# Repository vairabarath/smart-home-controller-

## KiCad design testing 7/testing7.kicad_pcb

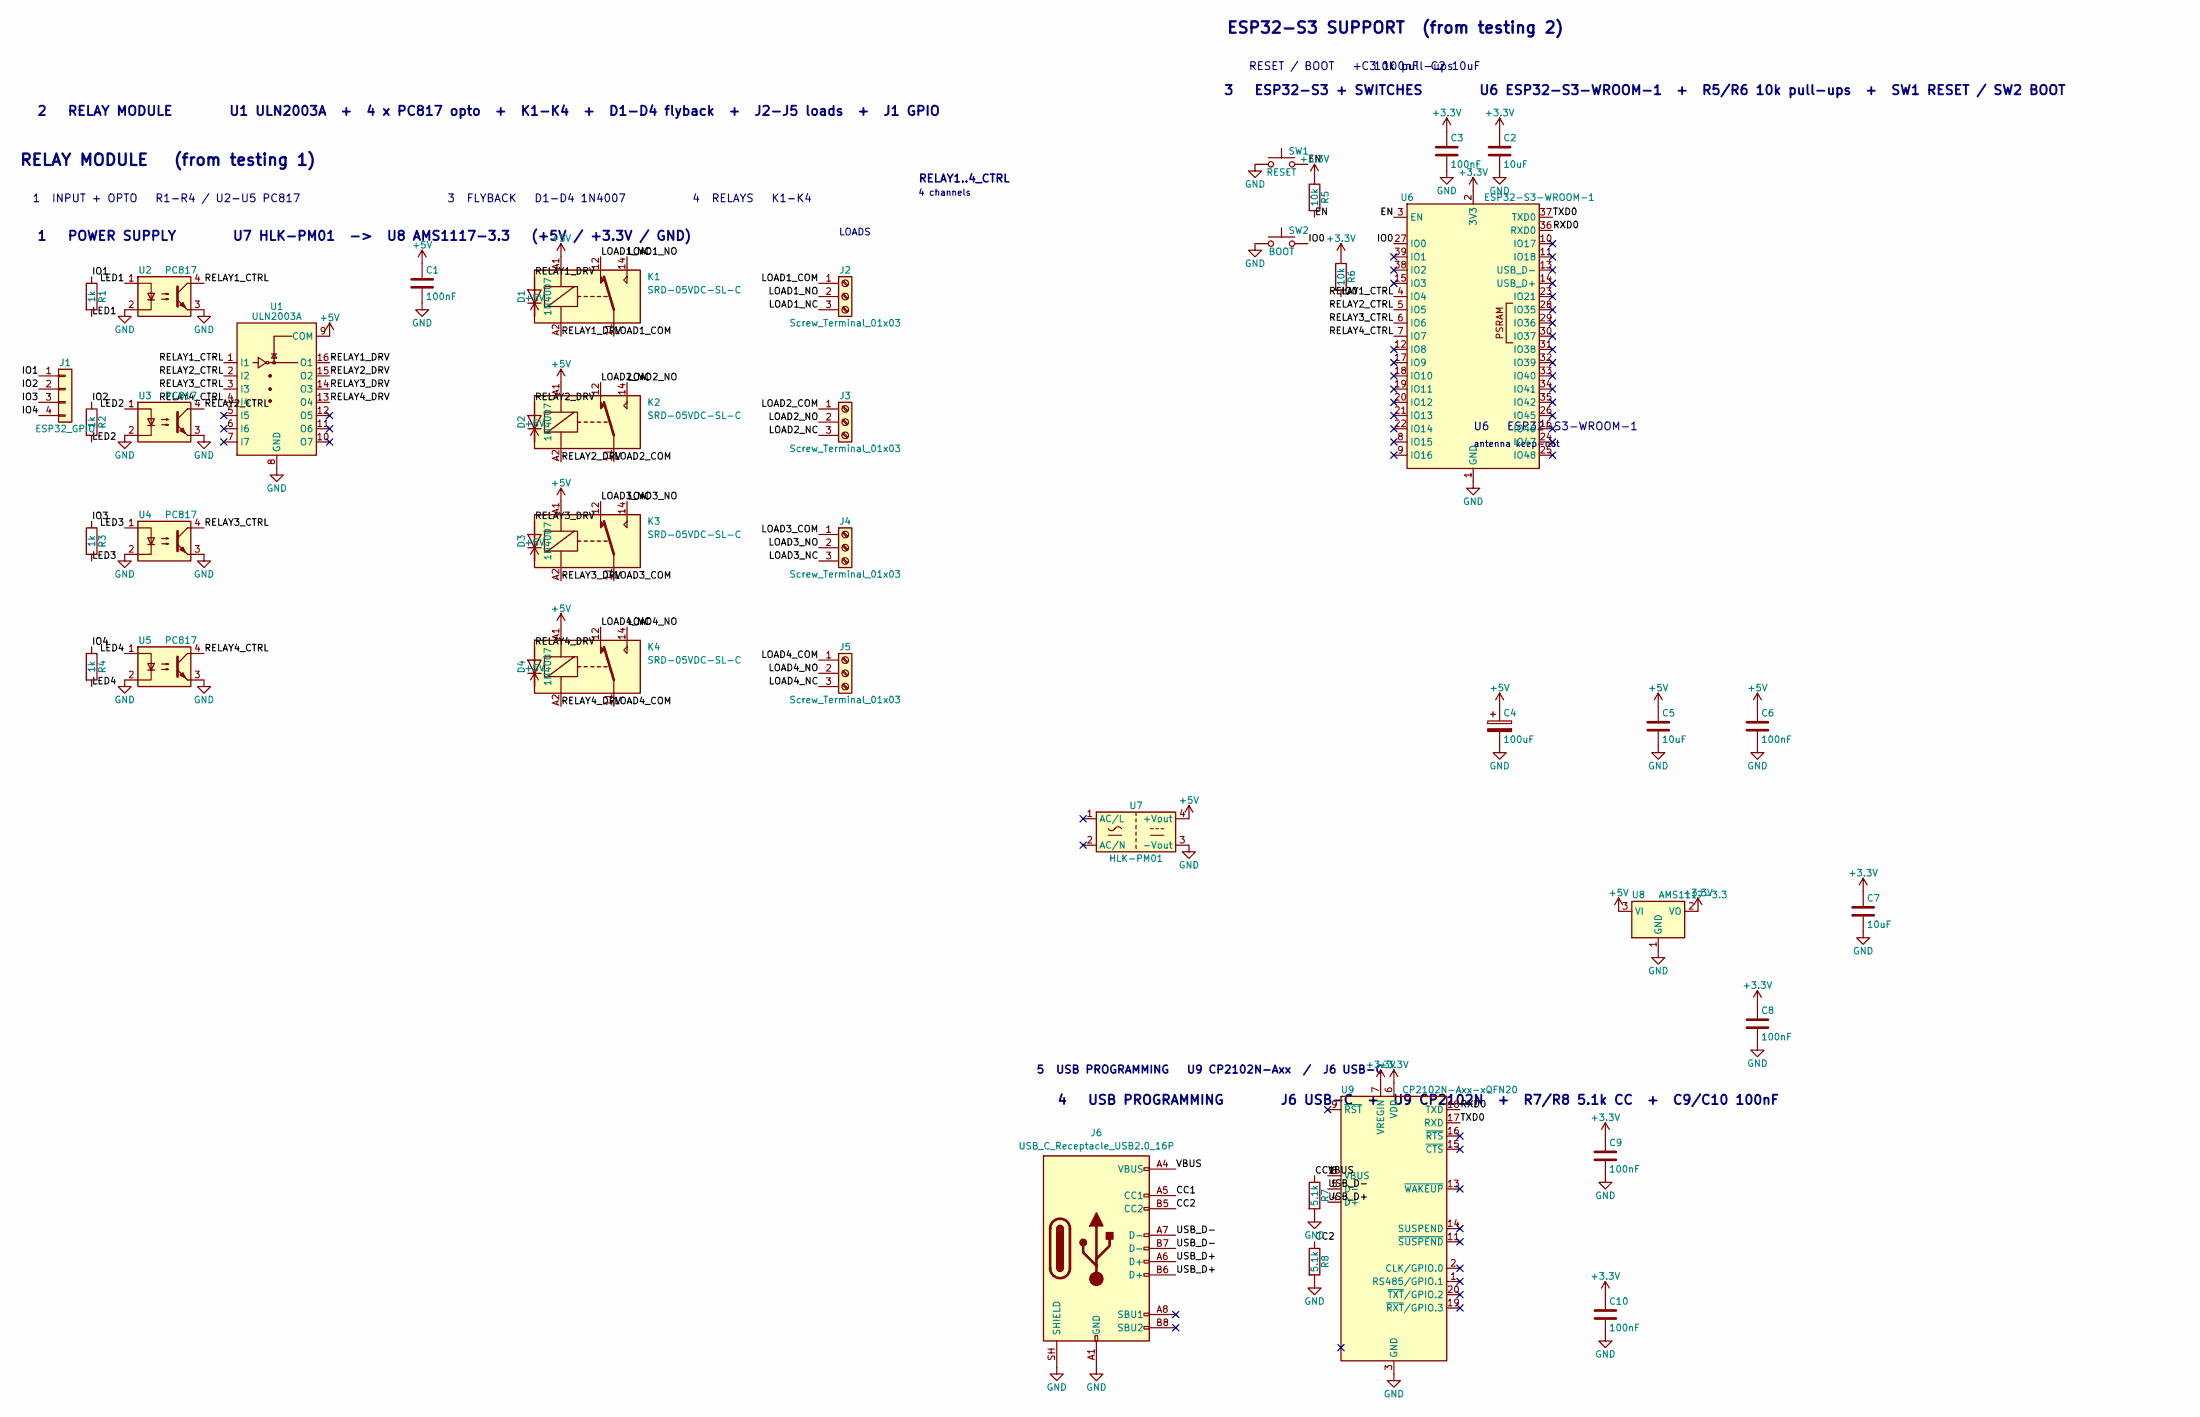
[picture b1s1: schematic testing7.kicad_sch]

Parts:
C1, C3, C6, C8, C9, C10: 100nF; C_0402_1005Metric
C2, C5, C7: 10uF; C_0805_2012Metric
C4: 100uF; CP_Radial_D10.0mm_P5.00mm
D1, D2, D3, D4: 1N4007; D_DO-41_SOD81_P10.16mm_Horizontal
J1: ESP32_GPIO; PinHeader_1x04_P2.54mm_Vertical
J2, J3, J4, J5: Screw_Terminal_01x03; TerminalBlock_Phoenix_MKDS-1,5-3_1x03_P5.00mm_Horizontal
J6: USB_C_Receptacle_USB2.0_16P; USB_C_Receptacle_GCT_USB4105-xx-A_16P_TopMnt_Horizontal
K1, K2, K3, K4: SRD-05VDC-SL-C; Relay_SPDT_Omron_G2RL-1-E
R1, R2, R3, R4: 1k; R_Axial_DIN0207_L6.3mm_D2.5mm_P7.62mm_Horizontal
R5, R6: 10k; R_0402_1005Metric
R7, R8: 5.1k; R_0402_1005Metric
SW1: RESET; SW_SPST_TL3342
SW2: BOOT; SW_SPST_TL3342
U1: ULN2003A; DIP-16_W7.62mm
U2, U3, U4, U5: PC817; DIP-4_W7.62mm
U6: ESP32-S3-WROOM-1
U7: HLK-PM01; Converter_ACDC_Hi-Link_HLK-PMxx
U8: AMS1117-3.3; SOT-223-3_TabPin2
U9: CP2102N-Axx-xQFN20; QFN-20-1EP_5x5mm_P0.65mm_EP3.35x3.35mm

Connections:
+3.3V: C2.1, C3.1, C7.1, C8.1, C9.1, C10.1, R5.1, R6.1, U6.2 (3V3), U8.2 (VO), U9.6 (VDD), U9.7 (VREGIN)
+5V: C1.1, C4.1, C5.1, C6.1, D1.1 (K), D2.1 (K), D3.1 (K), D4.1 (K), K1.A1, K2.A1, K3.A1, K4.A1, U1.9 (COM), U7.4 (+Vout), U8.3 (VI)
/CC1: J6.A5 (CC1), R7.1
/CC2: J6.B5 (CC2), R8.1
/EN: R5.2, SW1.2, U6.3 (EN)
/IO0: R6.2, SW2.2, U6.27 (IO0)
/IO1: J1.1, R1.1
/IO2: J1.2, R2.1
/IO3: J1.3, R3.1
/IO4: J1.4, R4.1
/LED1: R1.2, U2.1
/LED2: R2.2, U3.1
/LED3: R3.2, U4.1
/LED4: R4.2, U5.1
/LOAD1_COM: J2.1, K1.11
/LOAD1_NC: J2.3, K1.12
/LOAD1_NO: J2.2, K1.14
/LOAD2_COM: J3.1, K2.11
/LOAD2_NC: J3.3, K2.12
/LOAD2_NO: J3.2, K2.14
/LOAD3_COM: J4.1, K3.11
/LOAD3_NC: J4.3, K3.12
/LOAD3_NO: J4.2, K3.14
/LOAD4_COM: J5.1, K4.11
/LOAD4_NC: J5.3, K4.12
/LOAD4_NO: J5.2, K4.14
/RELAY1_CTRL: U1.1 (I1), U2.4, U6.4 (IO4)
/RELAY1_DRV: D1.2 (A), K1.A2, U1.16 (O1)
/RELAY2_CTRL: U1.2 (I2), U3.4, U6.5 (IO5)
/RELAY2_DRV: D2.2 (A), K2.A2, U1.15 (O2)
/RELAY3_CTRL: U1.3 (I3), U4.4, U6.6 (IO6)
/RELAY3_DRV: D3.2 (A), K3.A2, U1.14 (O3)
/RELAY4_CTRL: U1.4 (I4), U5.4, U6.7 (IO7)
/RELAY4_DRV: D4.2 (A), K4.A2, U1.13 (O4)
/RXD0: U6.36 (RXD0), U9.18 (TXD)
/TXD0: U6.37 (TXD0), U9.17 (RXD)
/USB_D+: J6.A6 (D+), J6.B6 (D+), U9.4 (D+)
/USB_D-: J6.A7 (D-), J6.B7 (D-), U9.5 (D-)
/VBUS: J6.A4 (VBUS), J6.A9 (VBUS), J6.B4 (VBUS), J6.B9 (VBUS), U9.8 (VBUS)
GND: C1.2, C2.2, C3.2, C4.2, C5.2, C6.2, C7.2, C8.2, C9.2, C10.2, J6.A1 (GND), J6.A12 (GND), J6.B1 (GND), J6.B12 (GND), J6.SH (SHIELD), R7.2, R8.2, SW1.1, SW2.1, U1.8 (GND), U2.2, U2.3, U3.2, U3.3, U4.2, U4.3, U5.2, U5.3, U6.1 (GND), U6.40 (GND), U6.41 (GND), U7.3 (-Vout), U8.1 (GND), U9.3 (GND), U9.12 (GND), U9.21 (GND)

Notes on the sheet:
RESET / BOOT + 10k pull-ups
antenna keep-out
C3 100nF C2 10uF
ESP32-S3 SUPPORT (from testing 2)
LOADS
RELAY1..4_CTRL
4 RELAYS K1-K4
4 channels
RELAY MODULE (from testing 1)
3 FLYBACK D1-D4 1N4007
1 INPUT + OPTO R1-R4 / U2-U5 PC817
U6 ESP32-S3-WROOM-1
5 USB PROGRAMMING U9 CP2102N-Axx / J6 USB-C
1 POWER SUPPLY U7 HLK-PM01 -> U8 AMS1117-3.3 (+5V / +3.3V / GND)
2 RELAY MODULE U1 ULN2003A + 4 x PC817 opto + K1-K4 + D1-D4 flyback + J2-J5 loads + J1 GPIO
3 ESP32-S3 + SWITCHES U6 ESP32-S3-WROOM-1 + R5/R6 10k pull-ups + SW1 RESET / SW2 BOOT
4 USB PROGRAMMING J6 USB-C + U9 CP2102N + R7/R8 5.1k CC + C9/C10 100nF

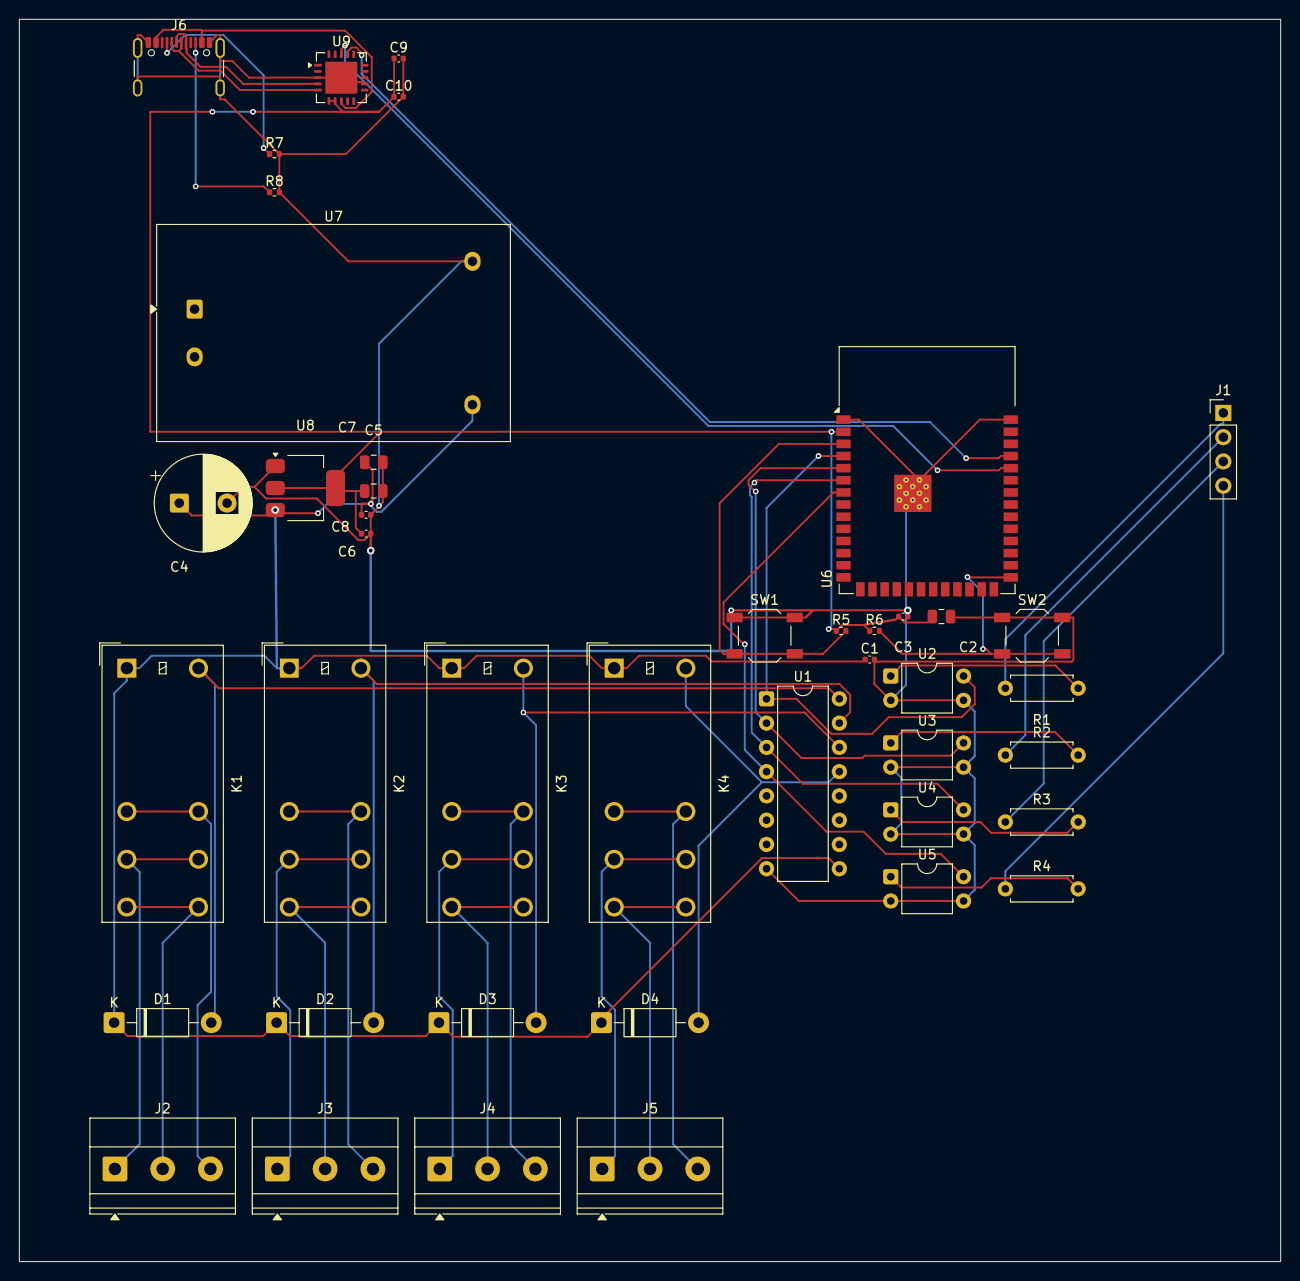
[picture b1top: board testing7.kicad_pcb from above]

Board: 2 copper layers, 132.0 x 130.0 mm, 43 parts (0 on the bottom side), 40 nets.

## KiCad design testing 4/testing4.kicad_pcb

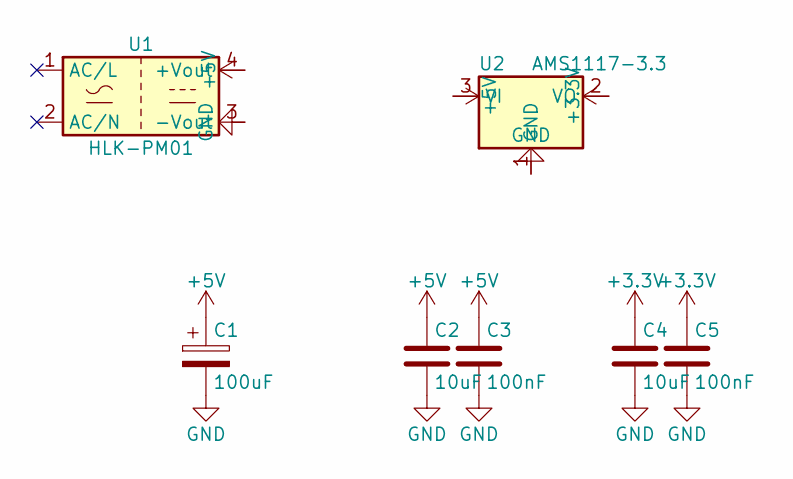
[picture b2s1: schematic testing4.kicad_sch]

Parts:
C1: 100uF; CP_Radial_D10.0mm_P5.00mm
C2, C4: 10uF; C_0805_2012Metric
C3, C5: 100nF; C_0402_1005Metric
U1: HLK-PM01; Converter_ACDC_Hi-Link_HLK-PMxx
U2: AMS1117-3.3; SOT-223-3_TabPin2

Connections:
+3.3V: C4.1, C5.1, U2.2 (VO)
+5V: C1.1, C2.1, C3.1, U1.4 (+Vout), U2.3 (VI)
GND: C1.2, C2.2, C3.2, C4.2, C5.2, U1.3 (-Vout), U2.1 (GND)

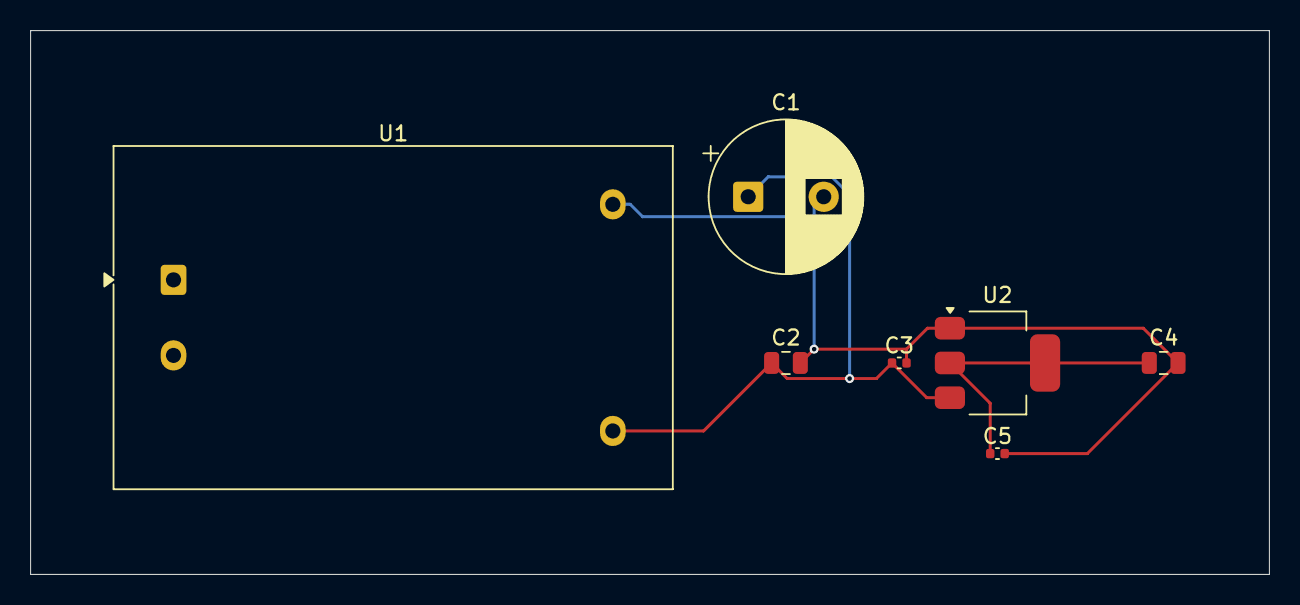
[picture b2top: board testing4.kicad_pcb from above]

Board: 2 copper layers, 82.0 x 36.0 mm, 7 parts (0 on the bottom side), 3 nets.

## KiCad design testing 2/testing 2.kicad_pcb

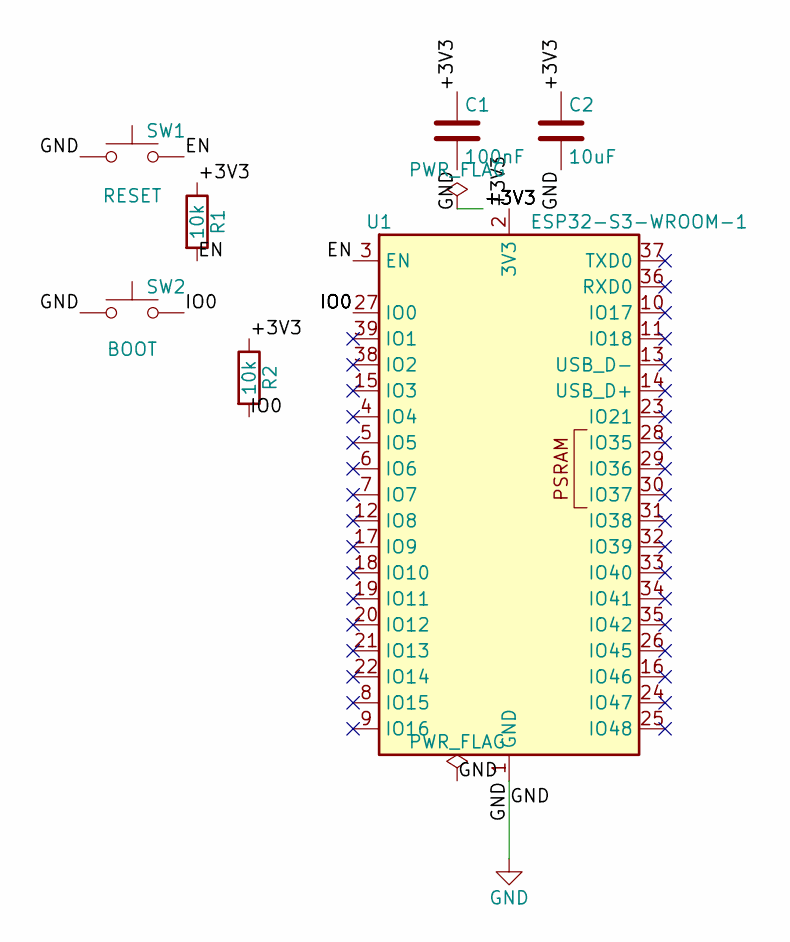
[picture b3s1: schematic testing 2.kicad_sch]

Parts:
C1: 100nF; C_0402_1005Metric
C2: 10uF; C_0603_1608Metric
R1, R2: 10k; R_0402_1005Metric
SW1: RESET; SW_SPST_TL3342
SW2: BOOT; SW_SPST_TL3342
U1: ESP32-S3-WROOM-1

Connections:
/+3V3: C1.1, C2.1, R1.1, R2.1, U1.2 (3V3)
/EN: R1.2, SW1.2, U1.3 (EN)
/IO0: R2.2, SW2.2, U1.27 (IO0)
GND: C1.2, C2.2, SW1.1, SW2.1, U1.1 (GND), U1.40 (GND), U1.41 (GND)

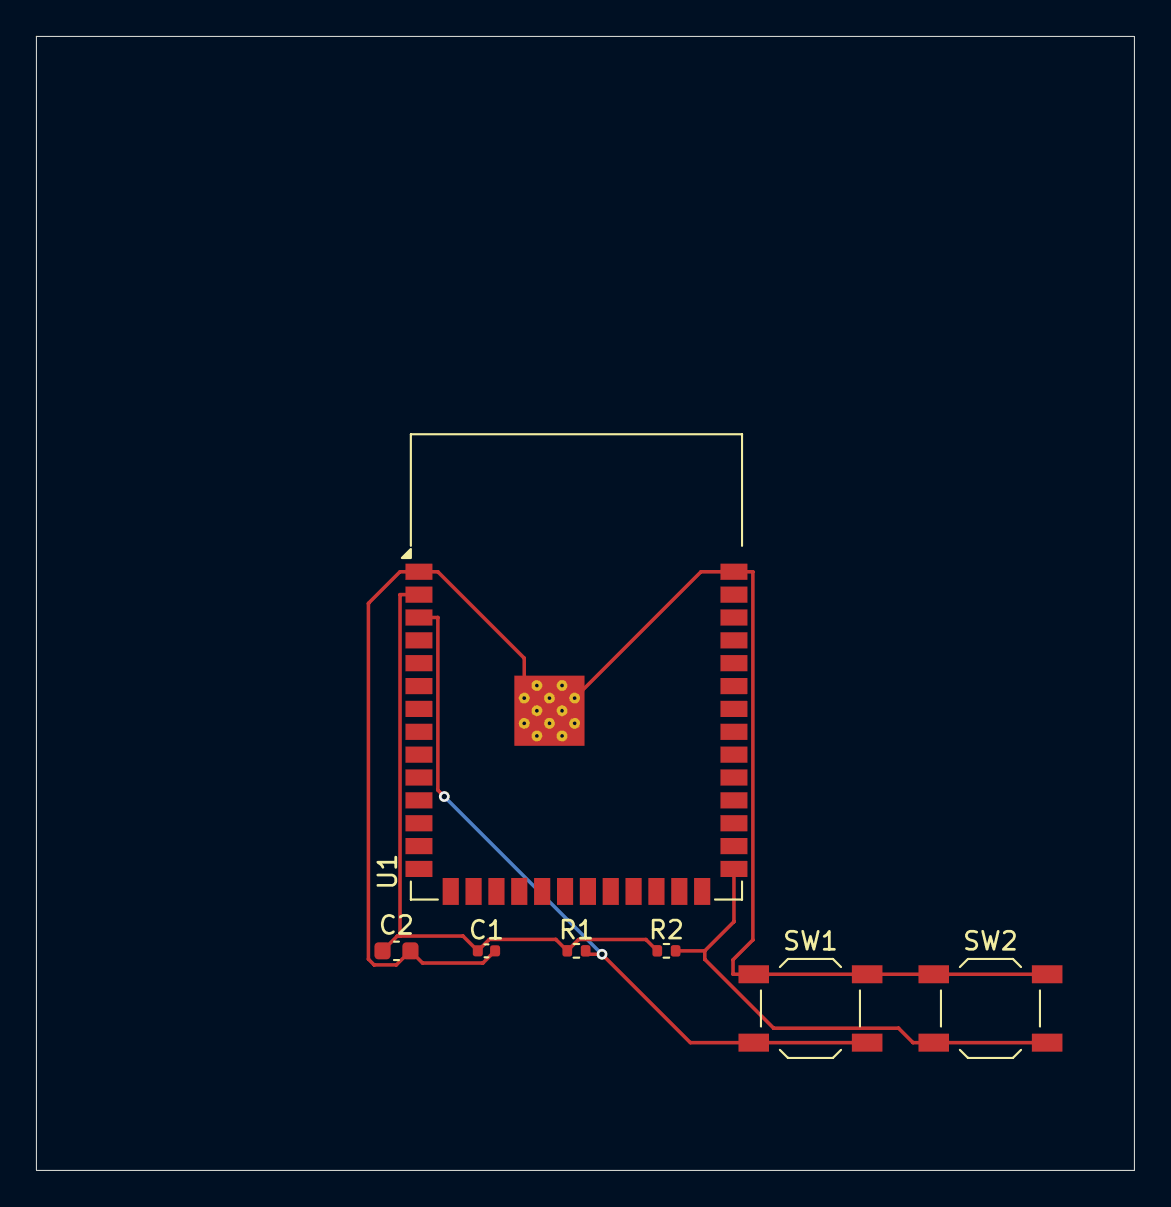
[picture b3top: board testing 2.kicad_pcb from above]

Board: 2 copper layers, 61.0 x 63.0 mm, 7 parts (0 on the bottom side), 4 nets.
